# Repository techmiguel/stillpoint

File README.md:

<h1 align="center">Stillpoint</h1>

<p align="center">
  <b>A privacy-first ceiling sensor that counts people, knows their posture and reports falls,<br>
  using a 60 GHz radar instead of a camera.</b>
</p>

<p align="center">

</p>

<p align="center"><a href="https://techmiguel.github.io/stillpoint/"><b>Project page →</b></a></p>

- **Sees the room, never the person.** No camera, no microphone. A 60 GHz FMCW radar
  (Infineon BGT60TR13C) measures where people are and how they move.
- **Finds people who are perfectly still**, by the movement of their chest as they
  breathe, so someone sitting or lying quietly does not "disappear".
- **Counts people, tracks position and posture, and reports falls**, all from one stream:
  no modes to switch between.
- **Runs entirely on the device** (Silicon Labs MGM260P / EFR32MG26) and reports over
  **Matter on Thread** with standard clusters: no cloud, no account, works with Home
  Assistant.
- **Open hardware**: KiCad schematic and 4-layer Ø60 mm board, FreeCAD enclosure, C
  firmware and the Python reference it is tested against.

> **Not a medical device.** A fall alert is a notification, never the only safety measure
> for a person.

## The board

| Top (ceiling side) | Bottom (radar, faces the floor) |
|---|---|
|  |  |

| | |
|---|---|
| Size | Ø60 mm round, 4 layers, 1.6 mm, ENIG, JLCPCB standard process |
| Radar | BGT60TR13C on the bottom face, 0.5 mm-pitch BGA, antennas in package |
| Radio + CPU | MGM260P module (Cortex-M33 + MVP accelerator, Matter/Thread/BLE) at the board edge with its antenna keep-out |
| Power | USB-C, 3.3 V LDO, 7 µVrms 1.8 V LDO for the radar, one π filter per radar supply domain |
| Extras | CP2102N USB console, RGB status LED, setup/reset buttons, Tag-Connect SWD, 14 test points |

Layout highlights:

- **Radar ground done by the book.** Solid ground on L2, a ground island on L3 right under
  the chip, nothing but ground vias inside the ball ring, and a custom DRC rule that keeps
  every other net off the inner layers under the radar.
- **Every radar supply is a straight lane** from its ball through 100 nF → 1 µF → 10 µF to
  its ferrite, with the smallest capacitor closest to the ball (Infineon's reference
  filter).
- **No crossing radar lines.** The radar signals leave the MCU from the pad row that faces
  the level translators, and the two translators are split over both faces to match the
  radar's ball order.

Fabrication files (Gerber, drill, BOM and CPL for JLCPCB, schematic PDF, STEP) are in
[`hardware/fabrication/`](hardware/fabrication) and attached to the
[rev A release](https://github.com/techmiguel/stillpoint/releases/tag/rev-a).
Full design notes: [docs/hardware.md](docs/hardware.md).

## The enclosure

A Ø65 mm, 24 mm tall ceiling puck on a Ø77 mm ceiling plate, 3D-printed in natural PETG.
The bottom of the shell is the radome: a flat slab exactly half a wavelength thick inside
the plastic (1.48 mm), so the 60 GHz signal passes through with about 0.15 dB of loss, and
the radar's antennas sit one wavelength (4.95 mm) above it. The board rests on three supports and the lid clamps it
with three posts at the same angles; the USB-C cable leaves through the lid, against the
ceiling.

The FreeCAD model ([`mechanical/enclosure.py`](mechanical/enclosure.py)) loads the real
board STEP and checks that nothing touches the shell, the lid or the radome, and that no
plastic sits in the antennas' ±60° field of view.

## How it works

```
ADC (3 RX × 32 chirps × 128 samples, 10 Hz)
  → range FFT ─┬─ motion path: MTI + Doppler + CFAR + angle   (people who move)
               └─ micro-motion path: 10 s of phase, breathing  (people who are still)
  → 3D detections → tracks with room logic (doors, occlusion, ghosts)
  → 66-byte feature record per track (the contract)
  → int8 CNN (14.6 KB) every 0.5 s → fail-safe decision → Matter
```

The fixes for the classic failures of commercial radar sensors are regression tests:

| Scenario | What the sensor does |
|---|---|
| A person sits still and someone walks in front of them | the hidden person is kept as *occluded*, never dropped |
| An empty room with a fan running | the fan is learned as an interferer and not counted |
| Someone walks next to a mirror | the mirror ghost is recognised as multipath |
| A fall | suspected by the model or by a fast drop to the floor, confirmed after 4 s still on the floor; if it cannot be verified it is reported as *uncertain*, never silenced ([plot](docs/img/fall_events.png)) |

The C firmware is checked frame by frame against the Python reference: same counts,
≥ 99.8 % identical quantized features, and identical postures, fall decisions and alarm
times ([plot](docs/img/app_c_vs_python.png)).

## License

[CERN-OHL-S-2.0](LICENSE) (CERN Open Hardware Licence v2, strongly reciprocal) for the
whole project: schematic, board, mechanics, firmware and documentation.

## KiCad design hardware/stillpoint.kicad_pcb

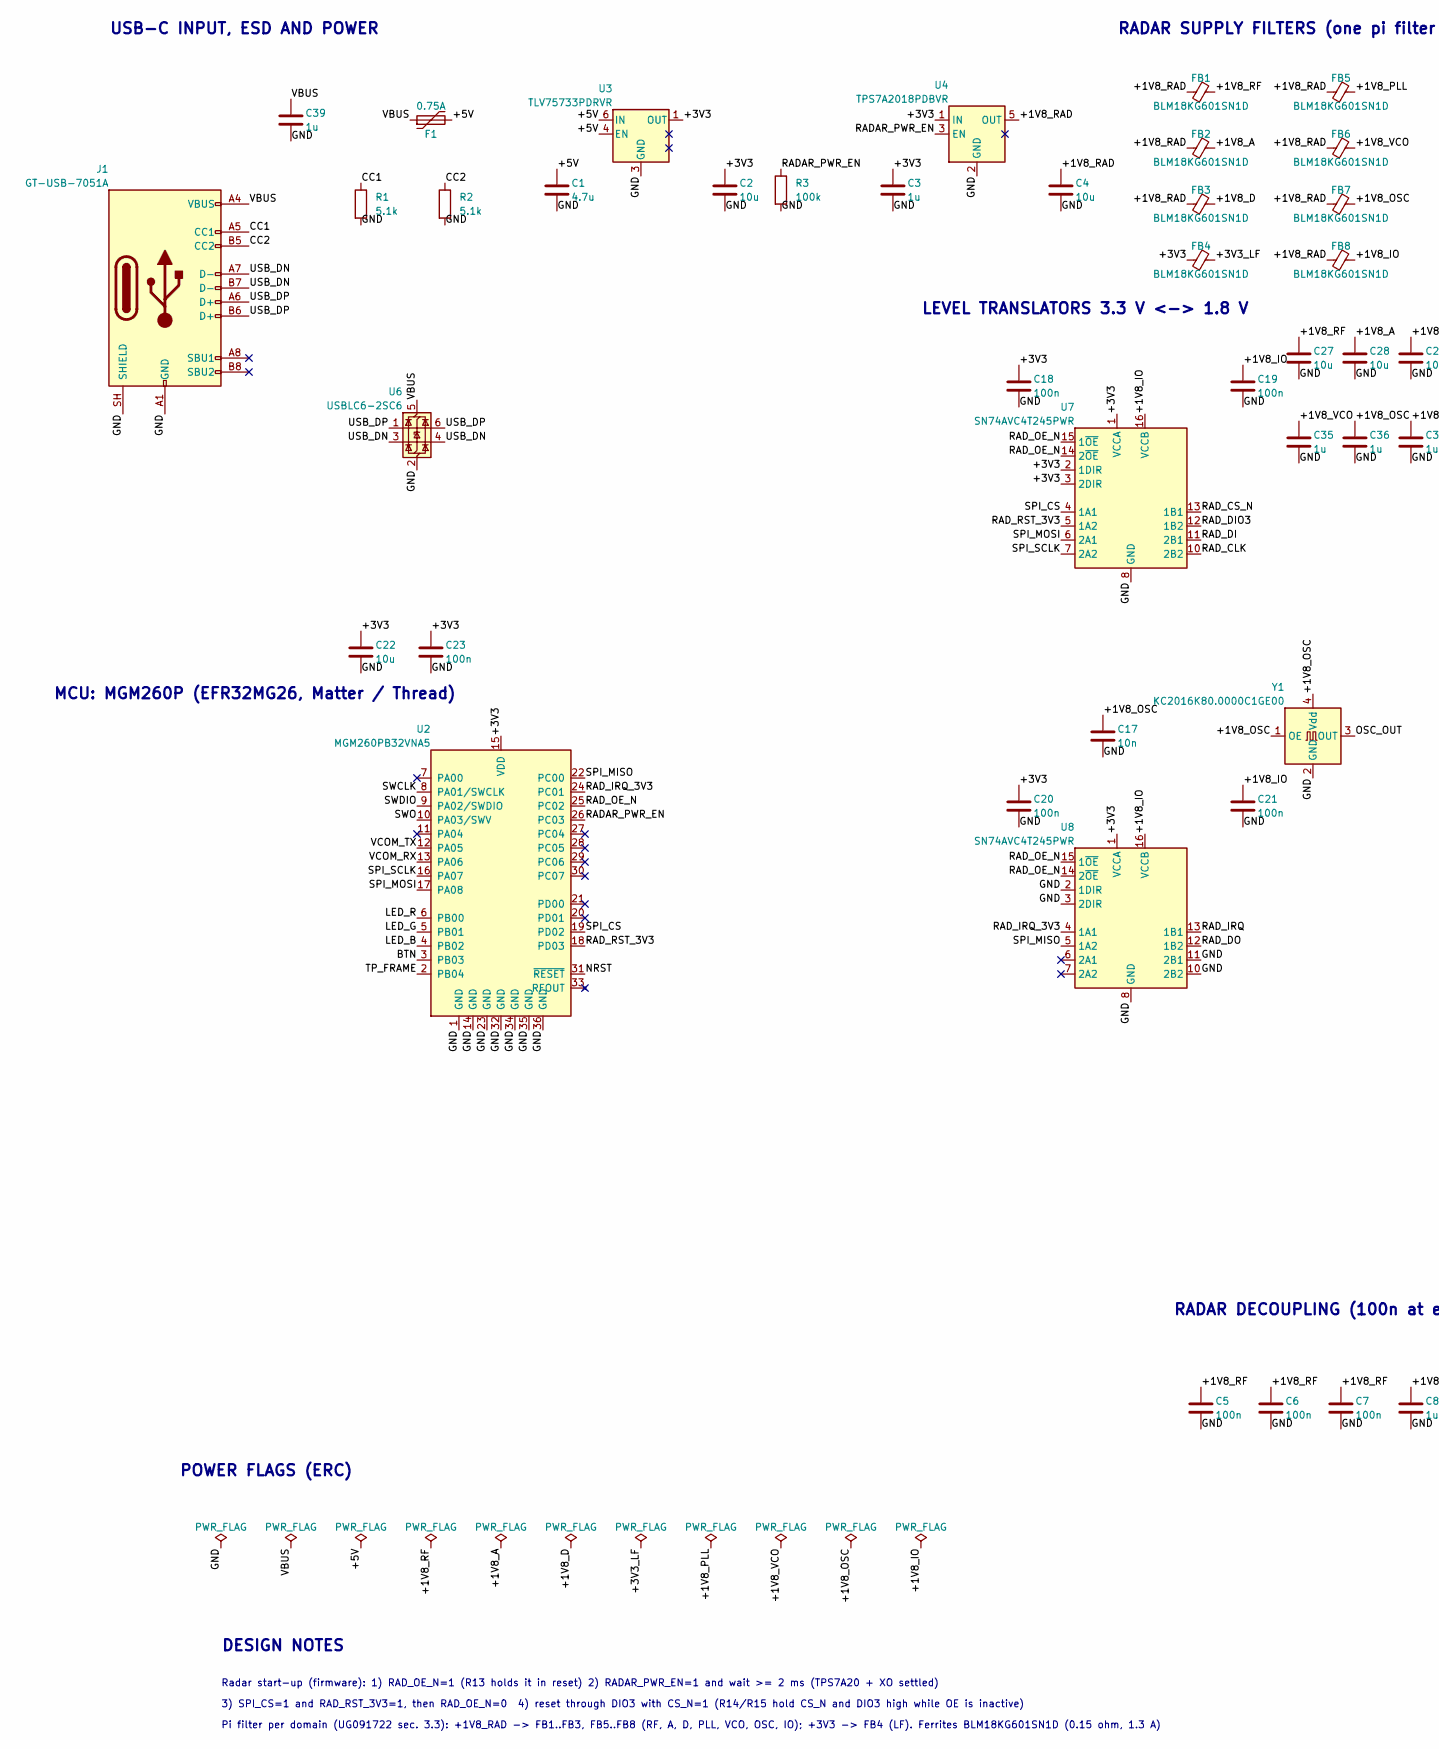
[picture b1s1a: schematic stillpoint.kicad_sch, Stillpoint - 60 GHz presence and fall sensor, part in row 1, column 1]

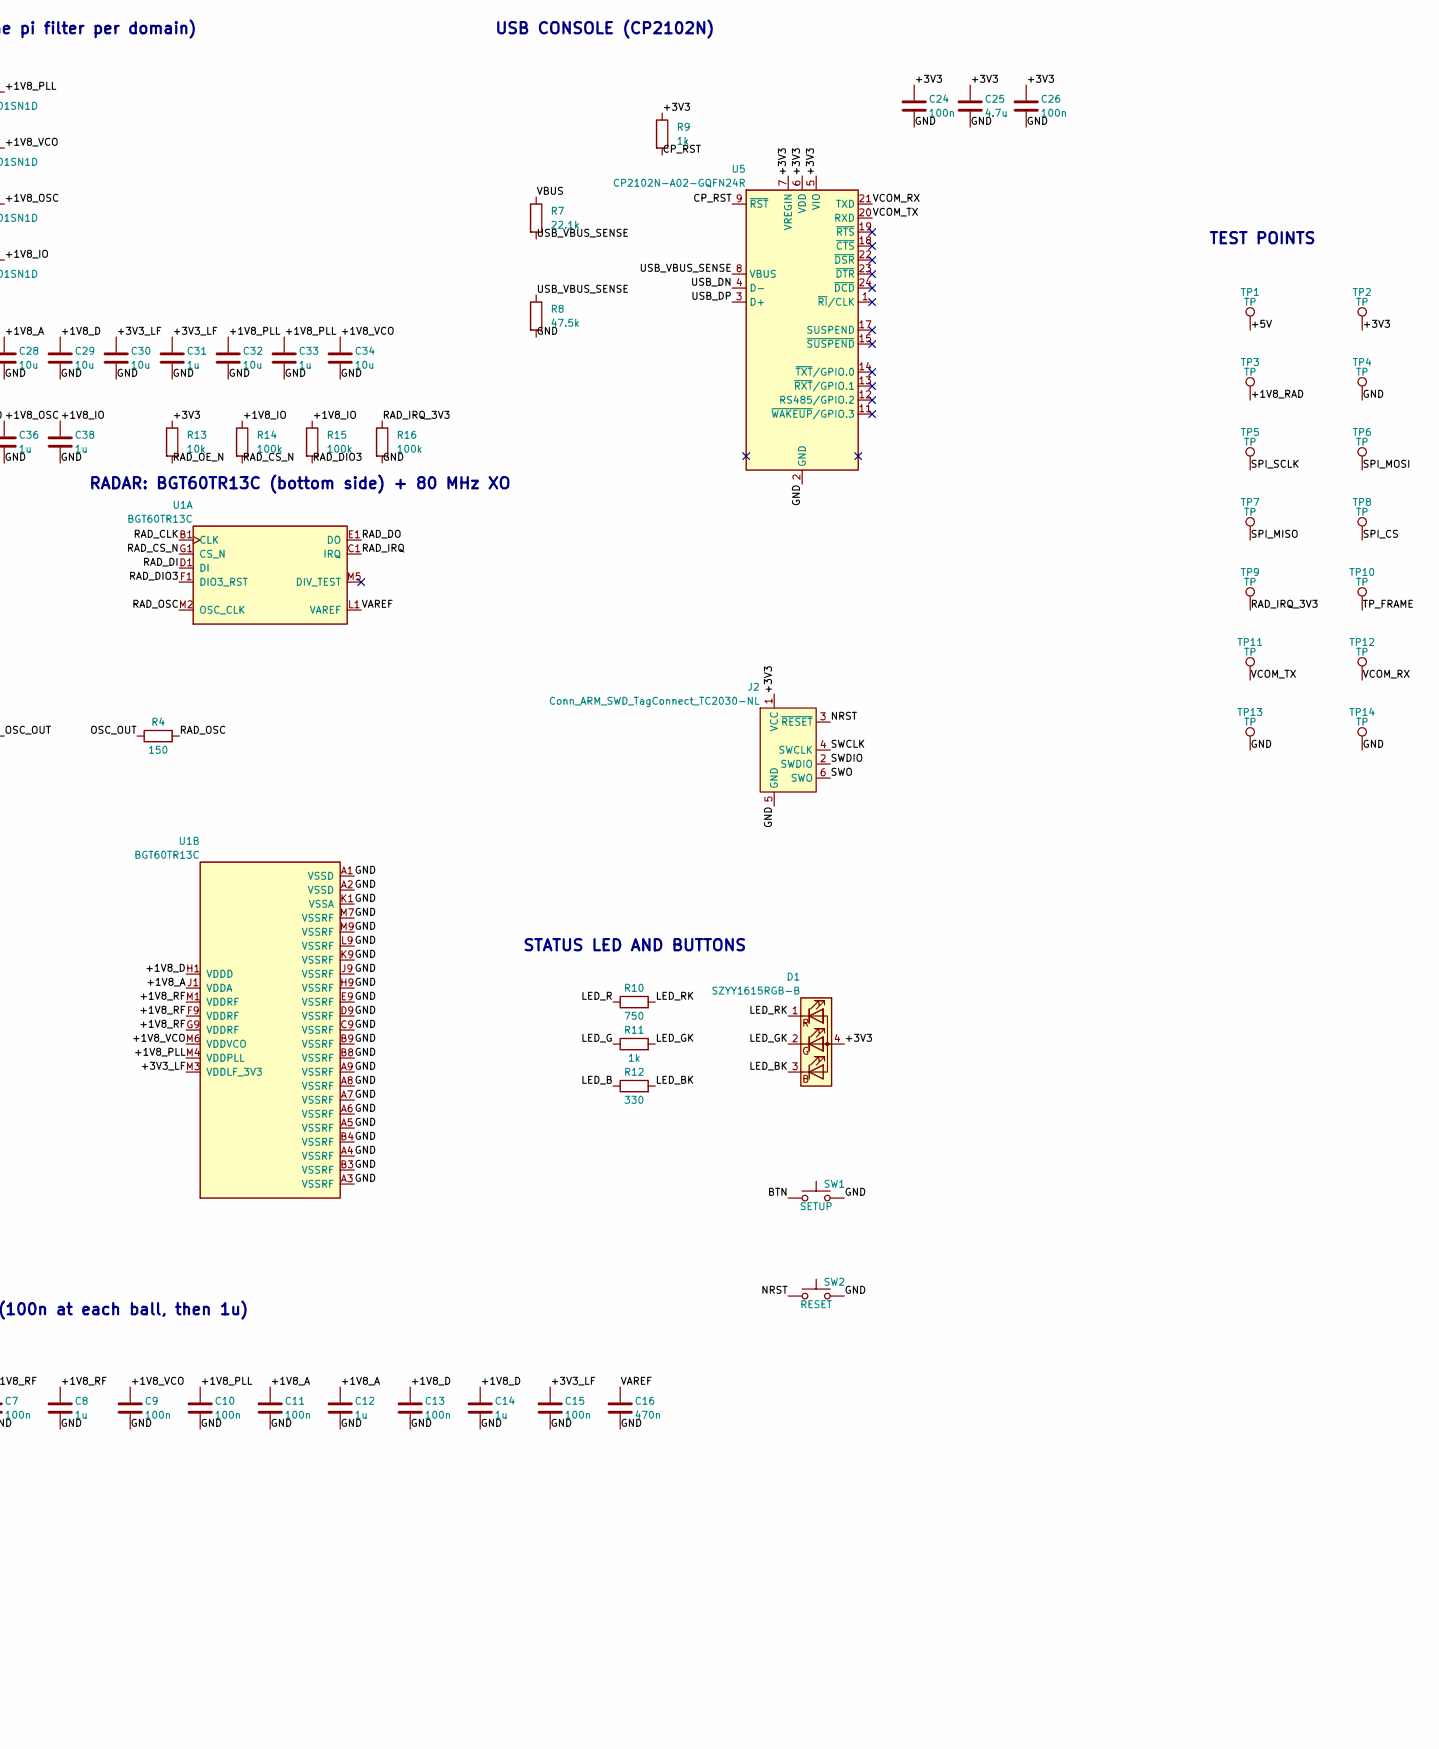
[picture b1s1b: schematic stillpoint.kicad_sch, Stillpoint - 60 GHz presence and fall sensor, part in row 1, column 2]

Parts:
C1: 4.7u; C_0805_2012Metric; Voltage 25V; MPN CL21A475KAQNNNE; LCSC C1779
C2, C4, C22, C27, C28, C29, C30, C32, C34: 10u; C_0805_2012Metric; Voltage 25V; MPN CL21A106KAYNNNE; LCSC C15850
C3, C8, C12, C14, C31, C33, C35, C36, C38, C39: 1u; C_0402_1005Metric; Voltage 25V; MPN CL05A105KA5NQNC; LCSC C52923
C5, C6, C7, C9, C10, C11, C13, C15, C18, C19, C20, C21, C23, C24, C26: 100n; C_0402_1005Metric; Voltage 16V; MPN CL05B104KO5NNNC; LCSC C1525
C16: 470n; C_0402_1005Metric; Voltage 16V; MPN CC0402KRX5R7BB474; LCSC C527010
C17: 10n; C_0402_1005Metric; Voltage 50V; MPN CL05B103KB5NNNC; LCSC C15195
C25: 4.7u; C_0402_1005Metric; Voltage 10V; MPN CC0402MRX5R6BB475; LCSC C469468
D1: SZYY1615RGB-B; LED_RGB_1615_SZYY1615RGB-B; MPN SZYY1615RGB-B; LCSC C3029071
F1: 0.75A; Fuse_1206_3216Metric; Voltage 8V; MPN SMD1206P075TFT; LCSC C545214
FB1, FB2, FB3, FB4, FB5, FB6, FB7, FB8: BLM18KG601SN1D; L_0603_1608Metric; MPN BLM18KG601SN1D; LCSC C85833
J1: GT-USB-7051A; USB_C_Receptacle_G-Switch_GT-USB-7051A; MPN GT-USB-7051A; LCSC C2843970
J2: Conn_ARM_SWD_TagConnect_TC2030-NL; Tag-Connect_TC2030-IDC-NL_2x03_P1.27mm_Vertical; MPN TC2030-IDC-NL
R1, R2: 5.1k; R_0402_1005Metric; MPN 0402WGF5101TCE; LCSC C25905
R3, R14, R15, R16: 100k; R_0402_1005Metric; MPN 0402WGF1003TCE; LCSC C25741
R4: 150; R_0402_1005Metric; MPN 0402WGF1500TCE; LCSC C25082
R7: 22.1k; R_0402_1005Metric; MPN 0402WGF2212TCE; LCSC C43473
R8: 47.5k; R_0402_1005Metric; MPN 0402WGF4752TCE; LCSC C25896
R9, R11: 1k; R_0402_1005Metric; MPN 0402WGF1001TCE; LCSC C11702
R10: 750; R_0402_1005Metric; MPN 0402WGF7500TCE; LCSC C25132
R12: 330; R_0402_1005Metric; MPN 0402WGF3300TCE; LCSC C25104
R13: 10k; R_0402_1005Metric; MPN 0402WGF1002TCE; LCSC C25744
SW1: SETUP; SW_SPST_TL3342; MPN TL3342F160QG; LCSC C2886898
SW2: RESET; SW_SPST_TL3342; MPN TL3342F160QG; LCSC C2886898
TP1, TP2, TP3, TP4, TP5, TP6, TP7, TP8, TP9, TP10, TP11, TP12, TP13, TP14: TP; TestPoint_Pad_D1.0mm
U1: BGT60TR13C; MPN BGT60TR13CE6327XUMA1; LCSC C3606641
U2: MGM260PB32VNA5; SiliconLabs_MGM260P_12.9x15mm; MPN MGM260PB32VNA5
U3: TLV75733PDRVR; WSON-6-1EP_2x2mm_P0.65mm_EP1x1.6mm; MPN TLV75733PDRVR; LCSC C2868428
U4: TPS7A2018PDBVR; SOT-23-5; MPN TPS7A2018PDBVR; LCSC C963430
U5: CP2102N-A02-GQFN24R; QFN-24-1EP_4x4mm_P0.5mm_EP2.6x2.6mm; MPN CP2102N-A02-GQFN24R; LCSC C969151
U6: USBLC6-2SC6; SOT-23-6; MPN USBLC6-2SC6; LCSC C7519
U7, U8: SN74AVC4T245PWR; TSSOP-16_4.4x5mm_P0.65mm; MPN SN74AVC4T245PWR; LCSC C81461
Y1: KC2016K80.0000C1GE00; Crystal_SMD_2016-4Pin_2.0x1.6mm; MPN KC2016K80.0000C1GE00; LCSC C1988243

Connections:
/+1V8_A: C11.1, C12.1, C28.1, FB2.2, U1.J1 (VDDA)
/+1V8_D: C13.1, C14.1, C29.1, FB3.2, U1.H1 (VDDD)
/+1V8_IO: C19.1, C21.1, C38.1, FB8.2, R14.1, R15.1, U7.16 (VCCB), U8.16 (VCCB)
/+1V8_OSC: C17.1, C36.1, FB7.2, Y1.1 (OE), Y1.4 (Vdd)
/+1V8_PLL: C10.1, C32.1, C33.1, FB5.2, U1.M4 (VDDPLL)
/+1V8_RAD: C4.1, FB1.1, FB2.1, FB3.1, FB5.1, FB6.1, FB7.1, FB8.1, TP3.1, U4.5 (OUT)
/+1V8_RF: C5.1, C6.1, C7.1, C8.1, C27.1, FB1.2, U1.F9 (VDDRF), U1.G9 (VDDRF), U1.M1 (VDDRF)
/+1V8_VCO: C9.1, C34.1, C35.1, FB6.2, U1.M6 (VDDVCO)
/+3V3: C2.1, C3.1, C18.1, C20.1, C22.1, C23.1, C24.1, C25.1, C26.1, D1.4 (A), FB4.1, J2.1 (VCC), R9.1, R13.1, TP2.1, U2.15 (VDD), U3.1 (OUT), U4.1 (IN), U5.5 (VIO), U5.6 (VDD), U5.7 (VREGIN), U7.1 (VCCA), U7.2 (1DIR), U7.3 (2DIR), U8.1 (VCCA)
/+3V3_LF: C15.1, C30.1, C31.1, FB4.2, U1.M3 (VDDLF_3V3)
/+5V: C1.1, F1.2, TP1.1, U3.4 (EN), U3.6 (IN)
/BTN: SW1.1, U2.3 (PB03)
/CC1: J1.A5 (CC1), R1.1
/CC2: J1.B5 (CC2), R2.1
/CP_RST: R9.2, U5.9 (~RST)
/GND: C1.2, C2.2, C3.2, C4.2, C5.2, C6.2, C7.2, C8.2, C9.2, C10.2, C11.2, C12.2, C13.2, C14.2, C15.2, C16.2, C17.2, C18.2, C19.2, C20.2, C21.2, C22.2, C23.2, C24.2, C25.2, C26.2, C27.2, C28.2, C29.2, C30.2, C31.2, C32.2, C33.2, C34.2, C35.2, C36.2, C38.2, C39.2, J1.A1 (GND), J1.A12 (GND), J1.B1 (GND), J1.B12 (GND), J1.SH (SHIELD), J2.5 (GND), R1.2, R2.2, R3.2, R8.2, R16.2, SW1.2, SW2.2, TP4.1, TP13.1, TP14.1, U1.A1 (VSSD), U1.A2 (VSSD), U1.A3 (VSSRF), U1.A4 (VSSRF), U1.A5 (VSSRF), U1.A6 (VSSRF), U1.A7 (VSSRF), U1.A8 (VSSRF), U1.A9 (VSSRF), U1.B3 (VSSRF), U1.B4 (VSSRF), U1.B8 (VSSRF), U1.B9 (VSSRF), U1.C9 (VSSRF), U1.D9 (VSSRF), U1.E9 (VSSRF), U1.H9 (VSSRF), U1.J9 (VSSRF), U1.K1 (VSSA), U1.K9 (VSSRF), U1.L9 (VSSRF), U1.M7 (VSSRF), U1.M9 (VSSRF), U2.1 (GND), U2.14 (GND), U2.23 (GND), U2.32 (GND), U2.34 (GND), U2.35 (GND), U2.36 (GND), U3.3 (GND), U3.7 (GND), U4.2 (GND), U5.2 (GND), U5.25 (GND), U6.2 (GND), U7.8 (GND), U7.9 (GND), U8.2 (1DIR), U8.3 (2DIR), U8.8 (GND), U8.9 (GND), U8.10 (2B2), U8.11 (2B1), Y1.2 (GND)
/LED_B: R12.1, U2.4 (PB02)
/LED_BK: D1.3 (BK), R12.2
/LED_G: R11.1, U2.5 (PB01)
/LED_GK: D1.2 (GK), R11.2
/LED_R: R10.1, U2.6 (PB00)
/LED_RK: D1.1 (RK), R10.2
/NRST: J2.3 (~RESET), SW2.1, U2.31 (~RESET)
/OSC_OUT: R4.1, Y1.3 (OUT)
/RADAR_PWR_EN: R3.1, U2.26 (PC03), U4.3 (EN)
/RAD_CLK: U1.B1 (CLK), U7.10 (2B2)
/RAD_CS_N: R14.2, U1.G1 (CS_N), U7.13 (1B1)
/RAD_DI: U1.D1 (DI), U7.11 (2B1)
/RAD_DIO3: R15.2, U1.F1 (DIO3_RST), U7.12 (1B2)
/RAD_DO: U1.E1 (DO), U8.12 (1B2)
/RAD_IRQ: U1.C1 (IRQ), U8.13 (1B1)
/RAD_IRQ_3V3: R16.1, TP9.1, U2.24 (PC01), U8.4 (1A1)
/RAD_OE_N: R13.2, U2.25 (PC02), U7.14 (2~OE), U7.15 (1~OE), U8.14 (2~OE), U8.15 (1~OE)
/RAD_OSC: R4.2, U1.M2 (OSC_CLK)
/RAD_RST_3V3: U2.18 (PD03), U7.5 (1A2)
/SPI_CS: TP8.1, U2.19 (PD02), U7.4 (1A1)
/SPI_MISO: TP7.1, U2.22 (PC00), U8.5 (1A2)
/SPI_MOSI: TP6.1, U2.17 (PA08), U7.6 (2A1)
/SPI_SCLK: TP5.1, U2.16 (PA07), U7.7 (2A2)
/SWCLK: J2.4 (SWCLK), U2.8 (PA01/SWCLK)
/SWDIO: J2.2 (SWDIO), U2.9 (PA02/SWDIO)
/SWO: J2.6 (SWO), U2.10 (PA03/SWV)
/TP_FRAME: TP10.1, U2.2 (PB04)
/USB_DN: J1.A7 (D-), J1.B7 (D-), U5.4 (D-), U6.3 (I/O2), U6.4 (I/O2)
/USB_DP: J1.A6 (D+), J1.B6 (D+), U5.3 (D+), U6.1 (I/O1), U6.6 (I/O1)
/USB_VBUS_SENSE: R7.2, R8.1, U5.8 (VBUS)
/VAREF: C16.1, U1.L1 (VAREF)
/VBUS: C39.1, F1.1, J1.A4 (VBUS), J1.A9 (VBUS), J1.B4 (VBUS), J1.B9 (VBUS), R7.1, U6.5 (VBUS)
/VCOM_RX: TP12.1, U2.13 (PA06), U5.21 (TXD)
/VCOM_TX: TP11.1, U2.12 (PA05), U5.20 (RXD)

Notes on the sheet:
USB-C INPUT, ESD AND POWER
RADAR SUPPLY FILTERS (one pi filter per domain)
USB CONSOLE (CP2102N)
TEST POINTS
MCU: MGM260P (EFR32MG26, Matter / Thread)
LEVEL TRANSLATORS 3.3 V <-> 1.8 V
RADAR: BGT60TR13C (bottom side) + 80 MHz XO
STATUS LED AND BUTTONS
RADAR DECOUPLING (100n at each ball, then 1u)
POWER FLAGS (ERC)
DESIGN NOTES
Radar start-up (firmware): 1) RAD_OE_N=1 (R13 holds it in reset) 2) RADAR_PWR_EN=1 and wait >= 2 ms (TPS7A20 + XO settled)
3) SPI_CS=1 and RAD_RST_3V3=1, then RAD_OE_N=0 4) reset through DIO3 with CS_N=1 (R14/R15 hold CS_N and DIO3 high while OE is inactive)
Pi filter per domain (UG091722 sec. 3.3): +1V8_RAD -> FB1..FB3, FB5..FB8 (RF, A, D, PLL, VCO, OSC, IO); +3V3 -> FB4 (LF). Ferrites BLM18KG601SN1D (0.15 ohm, 1.3 A)

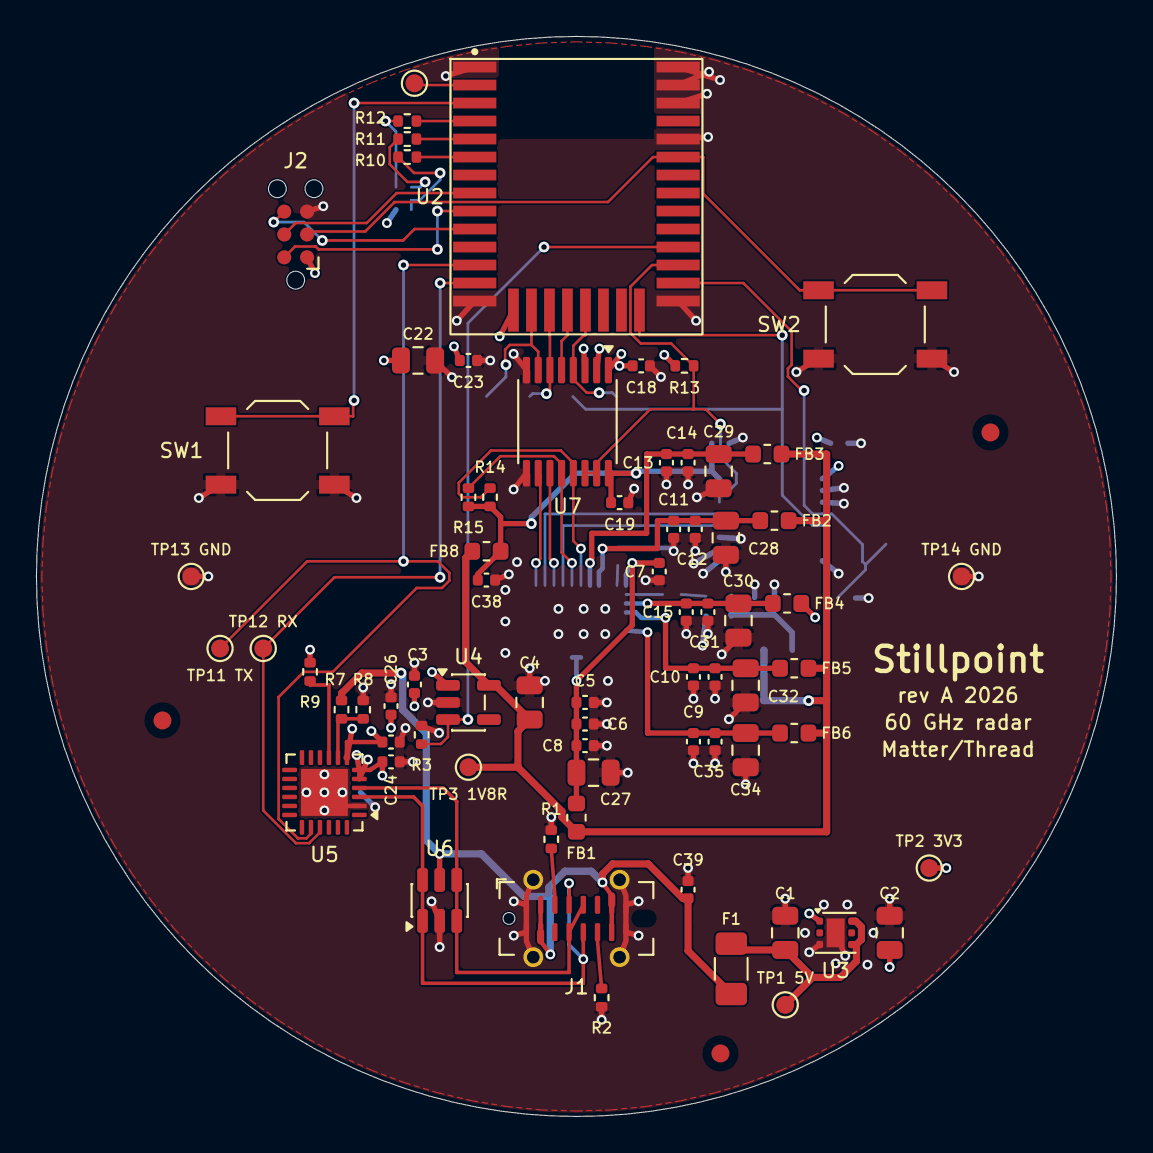
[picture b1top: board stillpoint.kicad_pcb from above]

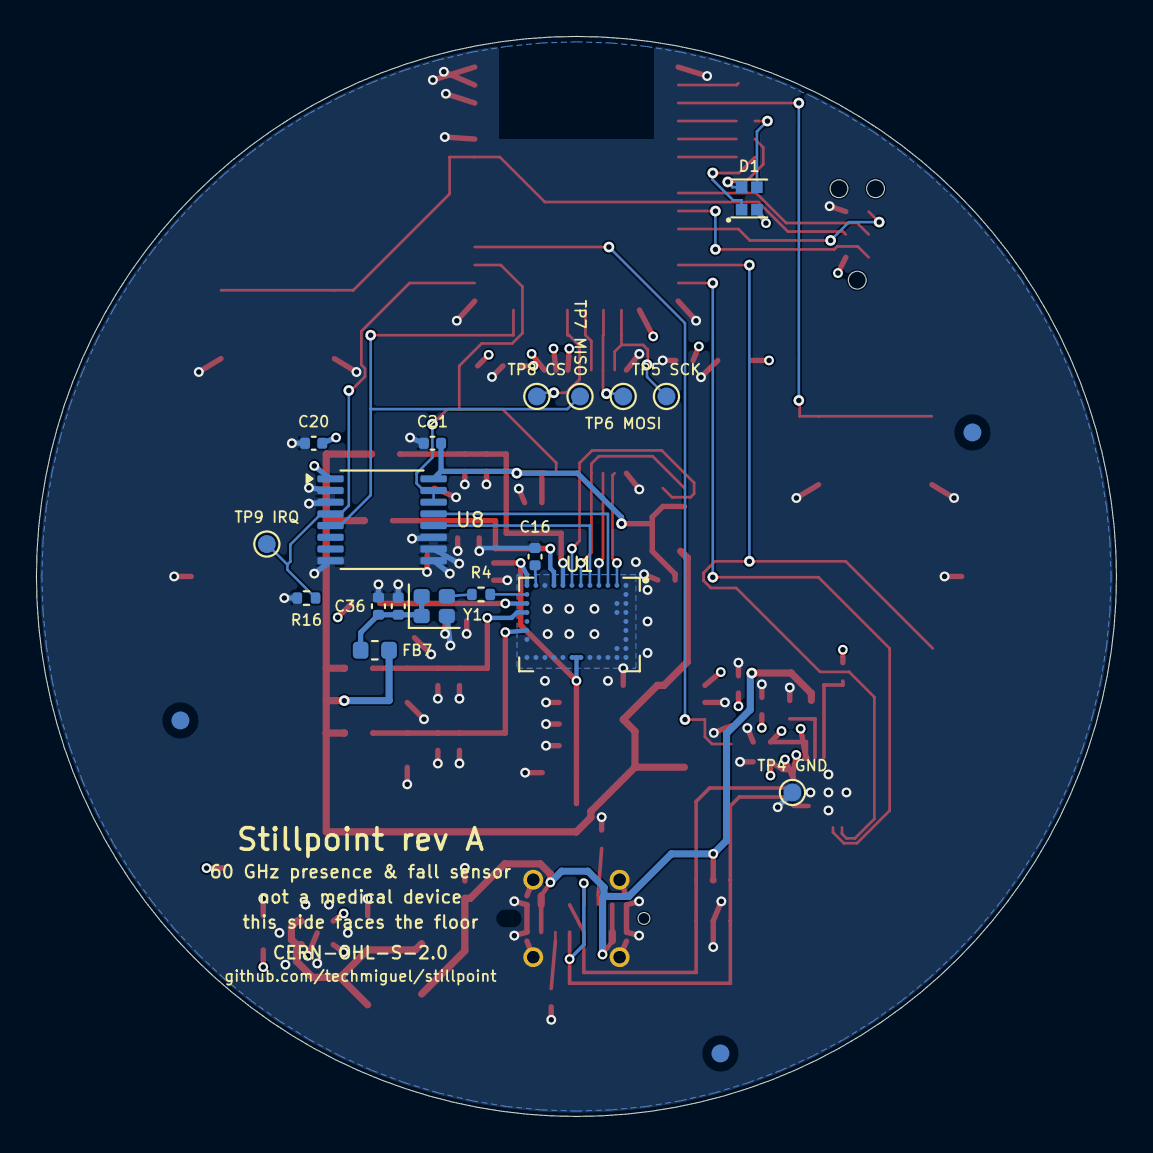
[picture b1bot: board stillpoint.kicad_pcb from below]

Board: 4 copper layers, 60.0 x 60.0 mm, 95 parts (21 on the bottom side), 50 nets.

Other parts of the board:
FID1, FID2, FID3, FID4, FID5, FID6: Fiducial; Fiducial_1mm_Mask2mm

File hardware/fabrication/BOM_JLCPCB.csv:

Comment,Designator,Footprint,LCSC Part #,Manufacturer,MPN,Qty
4.7u,C1,C_0805_2012Metric,C1779,Samsung,CL21A475KAQNNNE,1
10u,"C2,C4,C22,C27,C28,C29,C30,C32,C34",C_0805_2012Metric,C15850,Samsung,CL21A106KAYNNNE,9
1u,"C3,C8,C12,C14,C31,C33,C35,C36,C38,C39",C_0402_1005Metric,C52923,Samsung,CL05A105KA5NQNC,10
100n,"C5,C6,C7,C9,C10,C11,C13,C15,C18,C19,C20,C21,C23,C24,C26",C_0402_1005Metric,C1525,Samsung,CL05B104KO5NNNC,15
470n,C16,C_0402_1005Metric,C527010,YAGEO,CC0402KRX5R7BB474,1
10n,C17,C_0402_1005Metric,C15195,Samsung,CL05B103KB5NNNC,1
4.7u,C25,C_0402_1005Metric,C469468,YAGEO,CC0402MRX5R6BB475,1
SZYY1615RGB-B,D1,LED_RGB_1615_SZYY1615RGB-B,C3029071,Yongyu Photoelectric,SZYY1615RGB-B,1
0.75A,F1,Fuse_1206_3216Metric,C545214,PTTC,SMD1206P075TFT,1
BLM18KG601SN1D,"FB1,FB2,FB3,FB4,FB5,FB6,FB7,FB8",L_0603_1608Metric,C85833,Murata,BLM18KG601SN1D,8
GT-USB-7051A,J1,USB_C_Receptacle_G-Switch_GT-USB-7051A,C2843970,G-Switch,GT-USB-7051A,1
5.1k,"R1,R2",R_0402_1005Metric,C25905,UNI-ROYAL,0402WGF5101TCE,2
100k,"R3,R14,R15,R16",R_0402_1005Metric,C25741,UNI-ROYAL,0402WGF1003TCE,4
150,R4,R_0402_1005Metric,C25082,UNI-ROYAL,0402WGF1500TCE,1
22.1k,R7,R_0402_1005Metric,C43473,UNI-ROYAL,0402WGF2212TCE,1
47.5k,R8,R_0402_1005Metric,C25896,UNI-ROYAL,0402WGF4752TCE,1
1k,"R9,R11",R_0402_1005Metric,C11702,UNI-ROYAL,0402WGF1001TCE,2
750,R10,R_0402_1005Metric,C25132,UNI-ROYAL,0402WGF7500TCE,1
330,R12,R_0402_1005Metric,C25104,UNI-ROYAL,0402WGF3300TCE,1
10k,R13,R_0402_1005Metric,C25744,UNI-ROYAL,0402WGF1002TCE,1
SETUP,SW1,SW_SPST_TL3342,C2886898,E-Switch,TL3342F160QG,1
RESET,SW2,SW_SPST_TL3342,C2886898,E-Switch,TL3342F160QG,1
BGT60TR13C,U1,Infineon_PG-VF2BGA-40-1_6.5x5mm_P0.5mm,C3606641,Infineon,BGT60TR13CE6327XUMA1,1
MGM260PB32VNA5,U2,SiliconLabs_MGM260P_12.9x15mm,,Silicon Labs,MGM260PB32VNA5,1
TLV75733PDRVR,U3,WSON-6-1EP_2x2mm_P0.65mm_EP1x1.6mm,C2868428,Texas Instruments,TLV75733PDRVR,1
TPS7A2018PDBVR,U4,SOT-23-5,C963430,Texas Instruments,TPS7A2018PDBVR,1
CP2102N-A02-GQFN24R,U5,QFN-24-1EP_4x4mm_P0.5mm_EP2.6x2.6mm,C969151,Silicon Labs,CP2102N-A02-GQFN24R,1
USBLC6-2SC6,U6,SOT-23-6,C7519,STMicroelectronics,USBLC6-2SC6,1
SN74AVC4T245PWR,"U7,U8",TSSOP-16_4.4x5mm_P0.65mm,C81461,Texas Instruments,SN74AVC4T245PWR,2
KC2016K80.0000C1GE00,Y1,Crystal_SMD_2016-4Pin_2.0x1.6mm,C1988243,Kyocera AVX,KC2016K80.0000C1GE00,1

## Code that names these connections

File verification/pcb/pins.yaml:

# Critical pins copied from the DATASHEET (not from the schematic). Prefix ~ means regex.
# Rails that the rev A rework splits (RF/PLL/VCO, OSC, IO) use regexes so the
# check survives the rename; the ball/pin number is what must not move.

# Infineon BGT60TR13C, datasheet v2.4.6 Table 1 (PG-VF2BGA-40-1)
U1:
  B1: "~.*RAD_CLK"
  C1: "~.*RAD_IRQ"
  D1: "~.*RAD_DI"
  E1: "~.*RAD_DO"
  F1: "~.*RAD_DIO3"
  G1: "~.*RAD_CS_N"
  H1: "~.*1V8_D"
  J1: "~.*1V8_A"
  K1: GND
  L1: "~.*VAREF"
  M2: "~.*RAD_OSC"
  M3: "~.*3V3_LF"
  M4: "~.*1V8_(PLL|RF)"
  M6: "~.*1V8_(VCO|RF)"
  M1: "~.*1V8_RF"
  F9: "~.*1V8_RF"
  G9: "~.*1V8_RF"
  A1: GND
  A9: GND
  M9: GND

# Silicon Labs MGM260P, datasheet rev 1.1 Table 6.1 (pins 1-36)
U2:
  1: GND
  14: GND
  15: "+3V3"
  23: GND
  8: "~.*SWCLK"
  9: "~.*SWDIO"
  # Radar interface on the bottom pad row (EUSART1 routable to any port, Table 6.x);
  # PD00/PD01 (pads 21/20) left free for an optional 32.768 kHz crystal.
  16: "~.*SPI_SCLK"        # PA07
  17: "~.*SPI_MOSI"        # PA08
  18: "~.*RAD_RST_3V3"     # PD03
  19: "~.*SPI_CS"          # PD02
  22: "~.*SPI_MISO"        # PC00
  24: "~.*RAD_IRQ_3V3"     # PC01
  25: "~.*RAD_OE_N"        # PC02
  26: "~.*RADAR_PWR_EN"    # PC03
  12: "~.*VCOM_TX"         # PA05 (MCU RX)
  13: "~.*VCOM_RX"         # PA06 (MCU TX)
  3: "~.*BTN"              # PB03
  31: "~.*NRST"
  32: GND

# Silicon Labs CP2102N QFN24, datasheet section 5.2
U5:
  2: GND
  3: "~.*USB_DP"
  4: "~.*USB_DN"
  5: "+3V3"
  6: "+3V3"
  7: "+3V3"
  8: "~.*USB_VBUS_SENSE"
  9: "~.*CP_RST"
  20: "~.*VCOM_TX"
  21: "~.*VCOM_RX"

# ST USBLC6-2SC6, datasheet functional diagram (1/6 I/O1, 2 GND, 3/4 I/O2, 5 VBUS)
U6:
  2: GND
  5: "~.*VBUS"

# G-Switch GT-USB-7051A (USB-C 16P)
J1:
  A1: GND
  B12: GND
  A4: "~.*VBUS"
  B9: "~.*VBUS"
  A5: "~.*CC1"
  B5: "~.*CC2"
  A6: "~.*USB_DP"
  A7: "~.*USB_DN"

# Yongyu SZYY1615RGB-B (LCSC C3029071 symbol/footprint): 1 R, 2 G, 3 B cathodes, 4 common anode
D1:
  1: "~.*LED_RK"
  2: "~.*LED_GK"
  3: "~.*LED_BK"
  4: "+3V3"

# TI TLV75733P WSON-6 (DRV): 1 OUT, 3 GND, 4 EN, 6 IN, 7 thermal pad
U3:
  1: "+3V3"
  3: GND
  4: "+5V"
  6: "+5V"
  7: GND

# TI TPS7A2018 SOT-23-5 (DBV): 1 IN, 2 GND, 3 EN, 5 OUT
U4:
  1: "+3V3"
  2: GND
  3: "~.*RADAR_PWR_EN"
  5: "~.*1V8_RAD"

# Kyocera KC2016 XO: 1 ST, 2 GND, 3 OUT, 4 VCC
Y1:
  1: "~.*1V8_OSC"
  2: GND
  3: "~.*OSC_OUT"
  4: "~.*1V8_OSC"
